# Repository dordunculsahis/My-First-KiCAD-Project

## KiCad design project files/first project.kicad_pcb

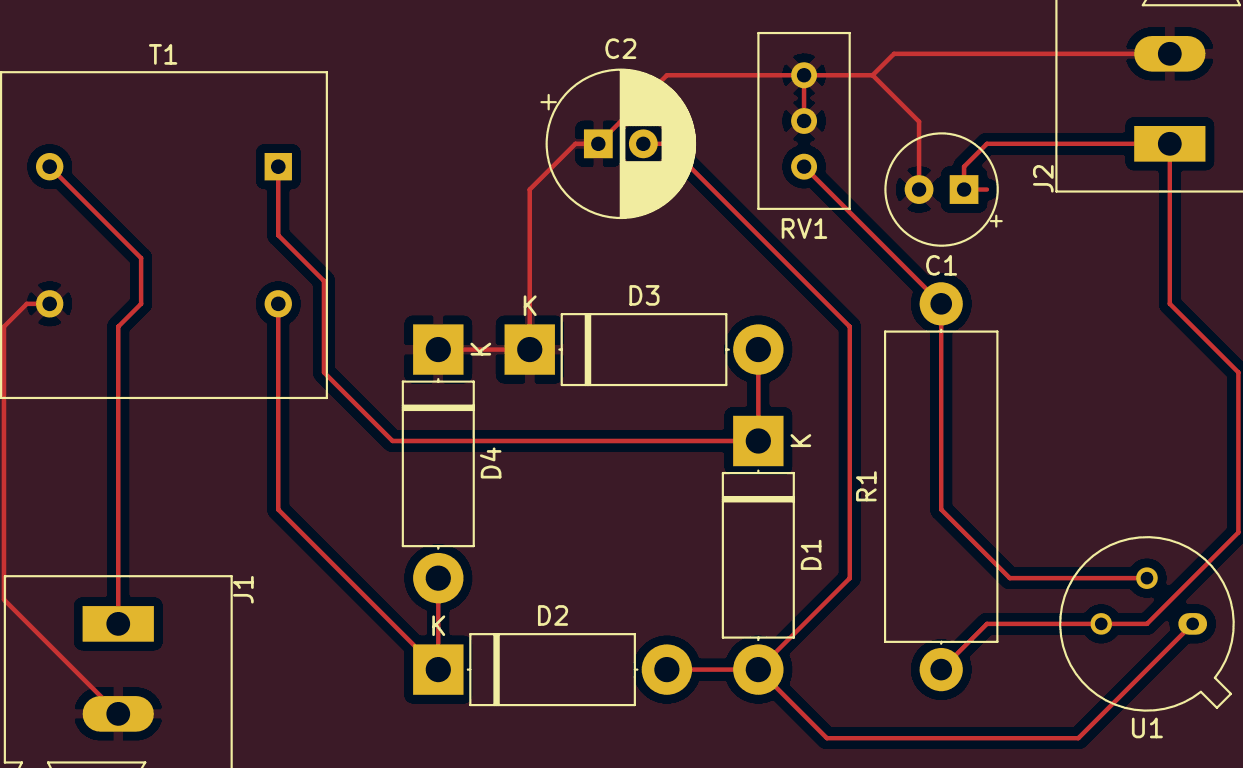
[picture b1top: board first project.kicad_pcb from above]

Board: 2 copper layers, 12 parts (0 on the bottom side), 7 nets.

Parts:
C1: 100u; CP_Radial_Tantal_D6.0mm_P2.50mm
C2: 2200u; CP_Radial_D8.0mm_P2.50mm
D1, D2, D3, D4: DIODE; D_5W_P12.70mm_Horizontal
J1, J2: klemens; TerminalBlock_Altech_AK300-2_P5.00mm
R1: 240; R_Axial_DIN0617_L17.0mm_D6.0mm_P20.32mm_Horizontal
RV1: 3.26k; Potentiometer_Bourns_3386C_Horizontal
T1: Transformer_1P_1S; Transformer_NF_ETAL_1-1_P1200
U1: LM317_TO39; TO-39-3

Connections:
GND: C1.2, C2.1, D3.1, D4.1, J1.2, J2.2, RV1.2, RV1.3, T1.2
unnamed: C1.1, J2.1, R1.1, U1.3
unnamed: C2.2, D1.2, D2.2, U1.1
unnamed: D1.1, D3.2, T1.3
unnamed: D2.1, D4.2, T1.4
unnamed: J1.1, T1.1
unnamed: R1.2, RV1.1, U1.2

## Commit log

2021-08-17 project files
    schematics, pcb, etc.
2021-08-17 gerber files
2021-08-17 pdf printouts
